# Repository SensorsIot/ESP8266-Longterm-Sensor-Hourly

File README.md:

# ESP8266-Longterm-Sensor-Hourly
ESP8266-Longterm Sensor Hourly 

This code belongs to a Youtube video: https://youtu.be/IYuYTfO6iOs

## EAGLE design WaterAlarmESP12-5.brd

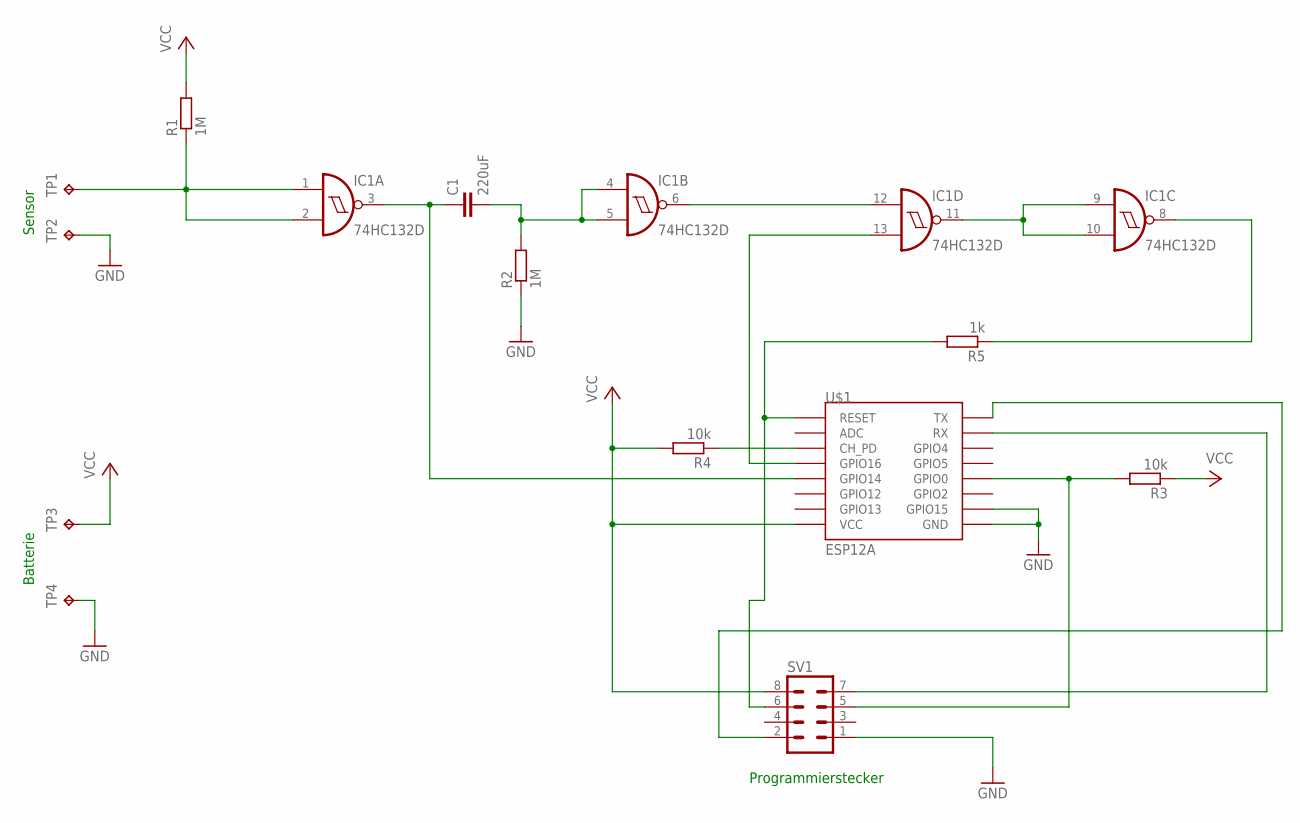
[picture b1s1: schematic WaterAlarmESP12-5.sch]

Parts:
C1: 220uF; C1206
IC1: 74HC132D; SO14
R1, R2: 1M; R1206
R3, R4: 10k; R1206
R5: 1k; R1206
SV1: MA04-2
TP1, TP2, TP3, TP4: TPPAD1-17; P1-17
U$1: ESP12A

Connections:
GND: IC1.7 (GND), R2.1, SV1.1, TP2.TP, TP4.TP, U$1.GND, U$1.GPIO15
unnamed: IC1.1 (I0), IC1.2 (I1), R1.1, TP1.TP
unnamed: R4.1, U$1.CH_PD
unnamed: C1.1, IC1.3 (O), U$1.GPIO14
unnamed: C1.2, IC1.4 (I0), IC1.5 (I1), R2.2
unnamed: IC1.6 (O), IC1.12 (I0)
unnamed: IC1.9 (I0), IC1.10 (I1), IC1.11 (O)
unnamed: R5.2, SV1.6, U$1.RESET
unnamed: IC1.13 (I1), U$1.GPIO16
unnamed: R3.2, SV1.5, U$1.GPIO0
unnamed: IC1.8 (O), R5.1
unnamed: SV1.2, U$1.TX
unnamed: SV1.7, U$1.RX
VCC: IC1.14 (VCC), R1.2, R3.1, R4.2, SV1.8, TP3.TP, U$1.VCC

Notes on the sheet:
Sensor
Batterie
Programmierstecker

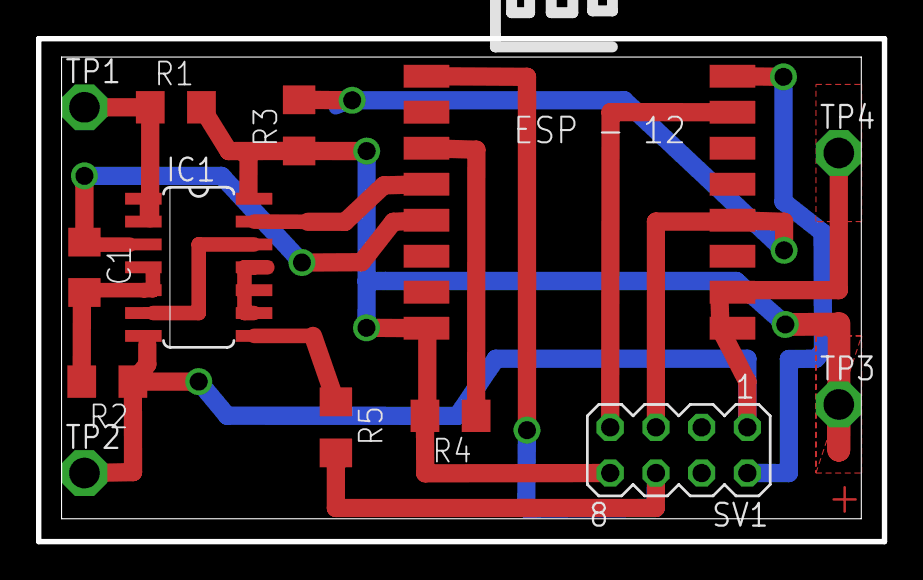
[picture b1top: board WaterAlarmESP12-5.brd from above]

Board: 2 copper layers, 47.0 x 27.9 mm, 13 parts (0 on the bottom side), 14 nets.

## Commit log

2016-05-05 :circus_tent: Added .gitattributes & .gitignore files
2016-05-05 ESP8266 sensor reads data and sents it to Spar,fun, ubidots, and mail
    deep sleep inbetween
2016-05-05 Deletion of HW files
2016-10-10 Float casting of ESP.getVcc()
